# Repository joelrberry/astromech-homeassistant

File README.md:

# droidrefit — an offline-first astromech droid

Custom MicroPython firmware for a stationary R2-D2 display build. It runs
**standalone** — three front-panel buttons drive the dome servo, sound, and
dome lights (tap mode ▲ / ▼ to cycle reactions, hold to adjust volume, tap
sound for a clip), with a piezo buzzer for feedback. WiFi + **Home Assistant**
(pick a reaction from a dashboard) are an optional layer, off by default; hold
**Mode ▲ + Sound** ~5 s to set up WiFi. No RC transmitter.

> **Repo name is historical.** This started as a firmware swap on a *CyberBrick*
> ESP32-C3 core board. That board browned out under servo + NeoPixels + WiFi,
> so the project moved to a plain **ESP32** with an external 5 V supply and a
> from-scratch modular firmware. The reverse-engineering writeup from that first
> chapter is [docs/cyberbrick-origins.md](docs/cyberbrick-origins.md).

## What's here

| Path | What |
|---|---|
| [`droidrefit/`](droidrefit/) | the firmware — `app/` package, `lib/`, `boot.py`, `main.py`, `package.json` (OTA manifest) |
| [`tools/deploy.py`](tools/deploy.py) | one-command host→board sync (`mpremote`), also the initial-load tool |
| [`hardware/droidrefit-pcb/`](hardware/droidrefit-pcb/) | KiCad carrier board — sockets the ESP32 devkit + DFPlayer, one 5 V rail, USB-C in. [DESIGN.md](hardware/droidrefit-pcb/DESIGN.md) |
| [`docs/firmware.md`](docs/firmware.md) | **the firmware reference** — architecture, boot flow, control surfaces, OTA, recovery |
| [`docs/dfplayer.md`](docs/dfplayer.md) | DFPlayer Mini — SD-card layout, adding sound clips, the serial protocol |
| [`docs/cyberbrick-origins.md`](docs/cyberbrick-origins.md) | the original CyberBrick writeup (retired board, but the LED/MQTT approach carried forward) |
| [`docs/project-notes.md`](docs/project-notes.md) | running history — decisions, bugs found and fixed |

## Hardware (as-built)

Plain ESP32 devkit · one dome servo (GPIO18) · DFPlayer Mini + speaker
(GPIO16/17, BUSY GPIO4) · 4× WS2812 dome lights (GPIO5, via a `74AHCT1G125`
level shifter) · 3 buttons (GPIO32/33/25, pin↔GND) · piezo buzzer (GPIO27) ·
optional SSD1306 OLED (I2C, GPIO21/22) · a shared **5 V, 3 A+**
rail everything hangs off directly. The
[carrier PCB](hardware/droidrefit-pcb/DESIGN.md) (100×70 mm, USB-C in,
JLCPCB-assembled) makes that permanent; a breadboard works for bench work if
you power the ESP32 over its own USB.

## Quick start

```
pip install mpremote
python3 tools/deploy.py --wipe
```

`deploy.py` stages the copy in safe mode and SHA-verifies every file, retrying
over a flaky USB link; a failed run leaves the board at a safe REPL, and
re-running converges. `--stay` leaves it in safe mode; `--format` reformats
the flash (last resort).

> **After flashing, hard power-cycle the board** (pull power / press EN — not
> just a soft reset). `deploy.py` ends with a soft reset, but hardware timers,
> the UART, PWM, and singleton driver objects survive that; only a cold boot
> gives the clean state the firmware actually runs in.

It boots straight into the app, **offline**. Buttons: **tap** mode ▲ / ▼ to
cycle the 7 reactions, **hold** to raise / lower volume, tap Sound for a clip.
The buzzer beeps to confirm.

**To add Home Assistant:** hold **Mode ▲ + Sound** together ~5 s → the board
reboots into a WiFi AP **`R2-D2-XXXX`**. Join it from a phone, the setup page
opens, enter WiFi + a droid name (tick "Connect to Home Assistant" for the MQTT
broker fields), save. It reboots onto your network and HA auto-discovers it
over MQTT (Mode / Sound / Volume + diagnostic sensors). No always-on web panel;
the portal exits on its own after 5 min idle, or via its Cancel link.

**Updates go over USB** — after an edit, `python3 tools/deploy.py`. On-device
OTA exists but is opt-in, needs `network_enabled`, and — on a classic ESP32 —
a plain-HTTP LAN mirror (`ota_url`), because it can't TLS to GitHub while the
app runs. Detail in [docs/firmware.md](docs/firmware.md).

## Recovery

- `noboot.txt` at the flash root → boot straight to a clean REPL (`deploy.py` uses this)
- hold **Mode ▲ + Sound** ~5 s → reboot into the WiFi setup portal (auto-exits after 5 min idle)
- hold the ESP32 BOOT button ~10 s while running → factory reset (wipe config, reboot to portal)
- a crash-looping OTA build auto-rolls-back after 3 failed boots

## Credits

- **The droid** — [*Build-A-Droid: CyberBrick based robot kit*](https://makerworld.com/en/models/1549117-build-a-droid-cyberbrick-based-robot-kit)
  by **Neebick** on MakerWorld. That's the printed astromech this firmware
  drives; this repo is only the electronics + software, not the model.
  Licensed Creative Commons (see the model page for the exact variant and
  follow its attribution / non-commercial / share-alike terms).
- **`droidrefit/lib/umqtt/simple.py`** — vendored **unmodified** from
  [micropython-lib](https://github.com/micropython/micropython-lib/blob/master/micropython/umqtt.simple/umqtt/simple.py)
  (MIT). MicroPython ships no MQTT client.
- **`droidrefit/lib/dfplayer.py`** — a minimal DFPlayer Mini (YX5200) UART
  driver written for this project; the frame/checksum protocol is per the
  DFPlayer Mini datasheet and the widely-published community command tables,
  not copied from a specific library.
- **`droidrefit/lib/ssd1306.py`** — vendored from
  [micropython-lib](https://github.com/micropython/micropython-lib/blob/master/micropython/drivers/display/ssd1306/ssd1306.py)
  (MIT), SPI variant trimmed off.
- **[MicroPython](https://micropython.org/)** (MIT) — the runtime.
- The earlier CyberBrick chapter leaned on CyberBrick's own `/bbl` driver
  library — see [docs/cyberbrick-origins.md](docs/cyberbrick-origins.md#acknowledgments).

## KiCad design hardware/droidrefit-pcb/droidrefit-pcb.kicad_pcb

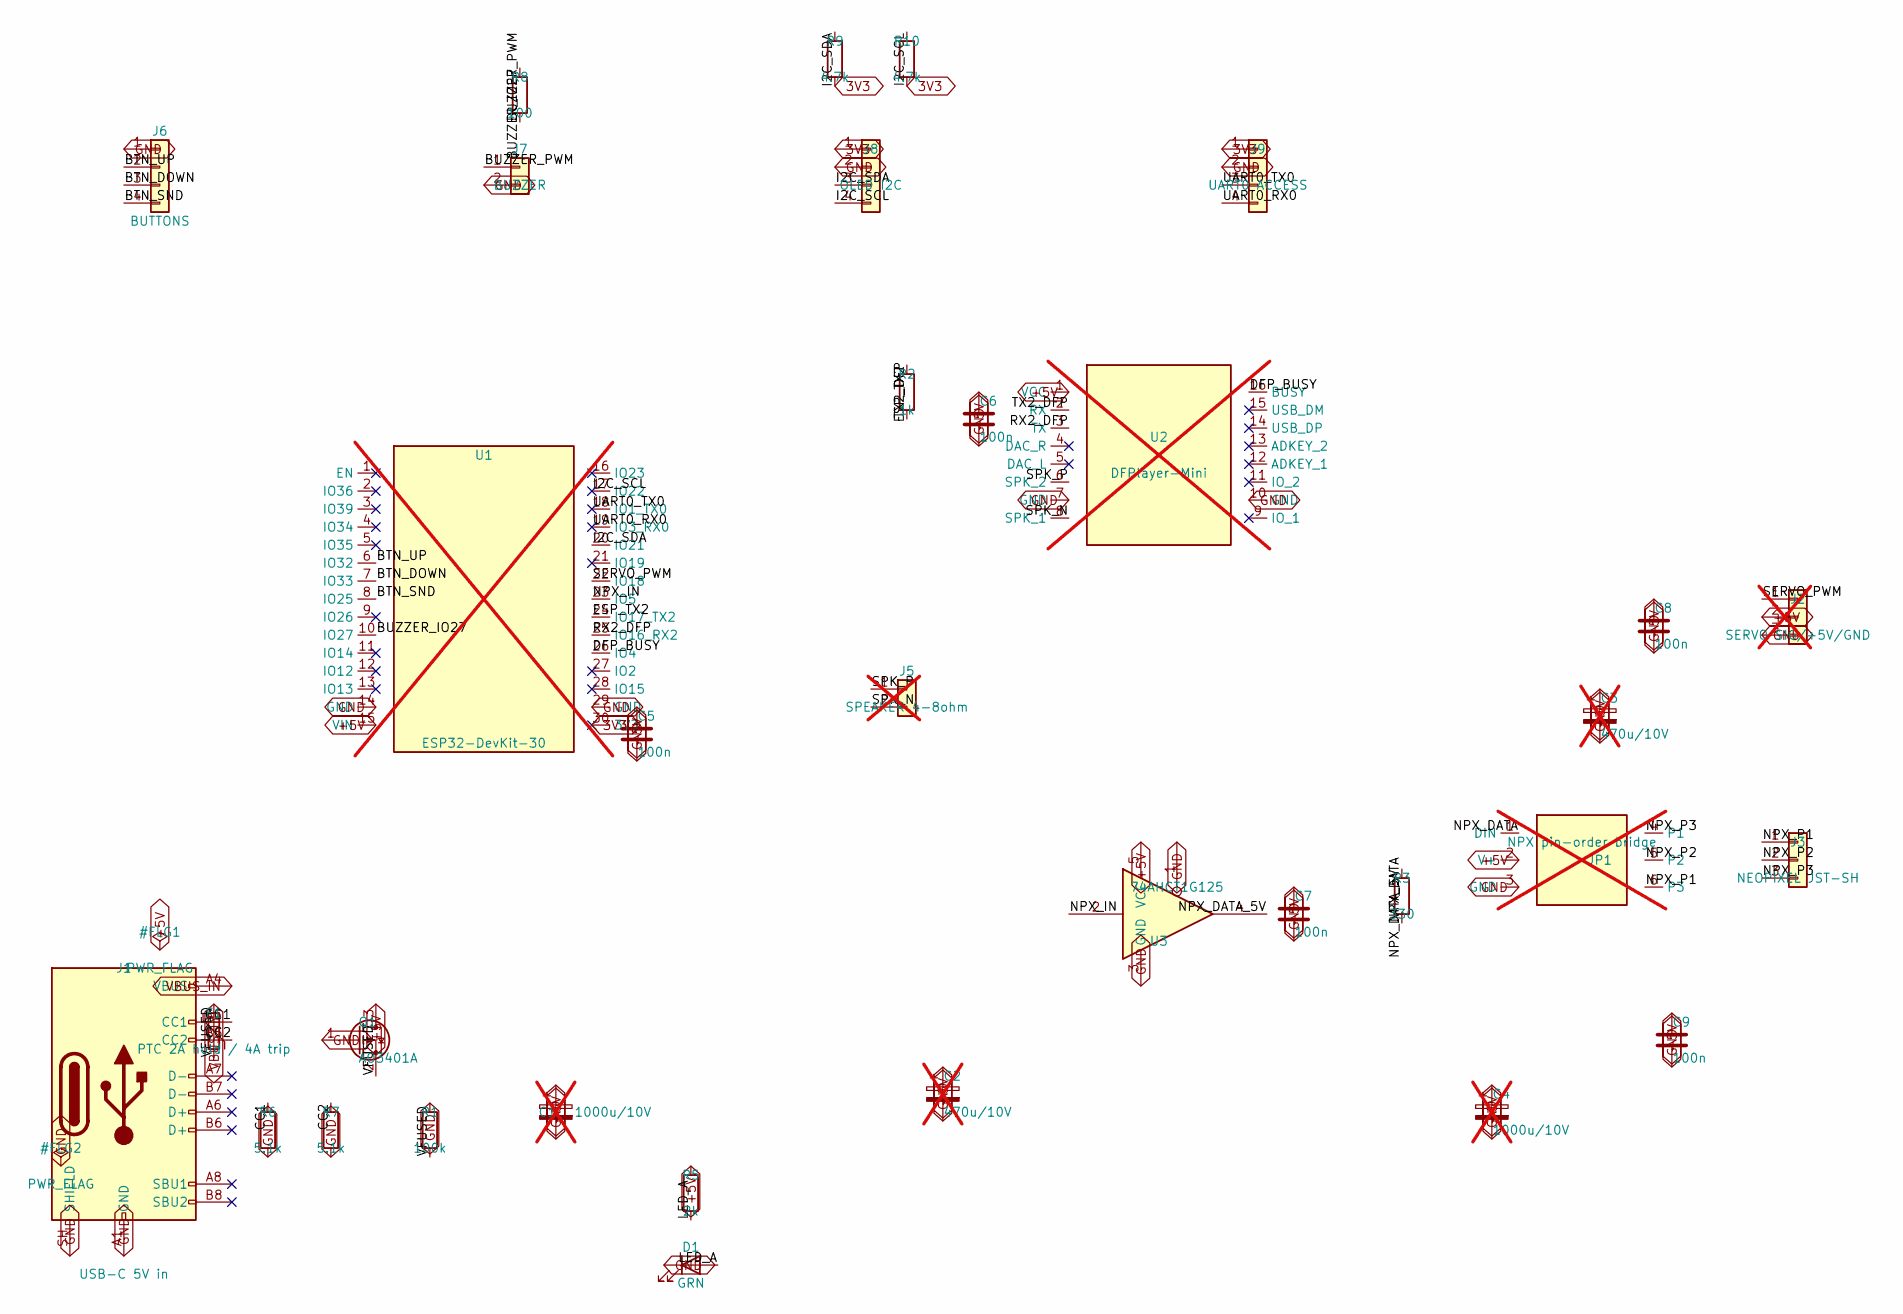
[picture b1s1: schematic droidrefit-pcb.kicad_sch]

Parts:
C1, C4: 1000u/10V; CP_Elec_8x10.5; MPN RVE1A102M0810; LCSC C310838; not fitted
C2, C3: 470u/10V; CP_Elec_6.3x7.7; MPN RVT1A471M0607; LCSC C335982; not fitted
C5, C6, C7, C8, C9: 100n; C_0603_1608Metric; MPN CC0603KRX7R9BB104; LCSC C14663
D1: GRN; LED_0603_1608Metric; MPN XL-1608UGC-04; LCSC C965804
F1: PTC 2A hold / 4A trip; Fuse_1812_4532Metric; MPN 1812L200/30GR; LCSC C18198342
J1: USB-C 5V in; USB_C_Receptacle_HCTL_HC-TYPE-C-16P-01A; MPN TYPE-C 16PIN 2MD; LCSC C2765186
J2: SERVO SIG/+5V/GND; PinHeader_1x03_P2.54mm_Vertical; MPN 1x3 2.54mm header; LCSC C49257; not fitted
J3: NEOPIXEL JST-SH; JST_SH_BM03B-SRSS-TB_1x03-1MP_P1.00mm_Vertical; MPN BM03B-SRSS-TB(LF)(SN); LCSC C160389
J5: SPEAKER 4-8ohm; JST_PH_B2B-PH-K_1x02_P2.00mm_Vertical; MPN B2B-PH-K-S; LCSC C131337; not fitted
J6: BUTTONS; PinHeader_1x04_P2.54mm_Vertical
J7: BUZZER; PinHeader_1x02_P2.54mm_Vertical
J8: OLED I2C; PinHeader_1x04_P2.54mm_Vertical
J9: UART0 ACCESS; PinHeader_1x04_P2.54mm_Vertical
JP1: NPX pin-order bridge; NeoPixel_Cfg_BridgeField_6; not fitted
Q1: AO3401A; SOT-23; MPN AO3401A; LCSC C15127
R1: 100k; R_0603_1608Metric; MPN 0603WAF1003T5E; LCSC C25803
R2: 1k; R_0603_1608Metric; MPN 0603WAF1001T5E; LCSC C21190
R3: 330; R_0603_1608Metric; MPN 0603WAF3300T5E; LCSC C23138
R5: 2k; R_0603_1608Metric; MPN 0603WAF2001T5E; LCSC C22975
R6, R7: 5.1k; R_0603_1608Metric; MPN 0603WAF5101T5E; LCSC C23186
R8: 100; R_0603_1608Metric
R9, R10: 4.7k; R_0603_1608Metric
U1: ESP32-DevKit-30; ESP32_DevKit_30pin_Socket_24p5mm; not fitted
U2: DFPlayer-Mini; DFPlayer_Mini_Socket; not fitted
U3: 74AHCT1G125; SOT-23-5; MPN SN74AHCT1G125DBVR; LCSC C7484

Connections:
3V3: J8.1, J9.1, R9.2, R10.2, U1.30 (3V3)
+5V: C1.1, C2.1, C3.1, C4.1, C5.1, C6.1, C7.1, C8.1, C9.1, J2.2, JP1.2 (V+), Q1.3 (D), R5.1, U1.15 (VIN), U2.1 (VCC), U3.5 (VCC)
BTN_DOWN: J6.3, U1.7 (IO33)
BTN_SND: J6.4, U1.8 (IO25)
BTN_UP: J6.2, U1.6 (IO32)
BUZZER_IO27: R8.1, U1.10 (IO27)
BUZZER_PWM: J7.1, R8.2
CC1: J1.A5 (CC1), R6.1
CC2: J1.B5 (CC2), R7.1
DFP_BUSY: U1.26 (IO4), U2.16 (BUSY)
ESP_TX2: R2.1, U1.24 (IO17_TX2)
GND: C1.2, C2.2, C3.2, C4.2, C5.2, C6.2, C7.2, C8.2, C9.2, D1.1 (K), J1.A1 (GND), J1.A12 (GND), J1.B1 (GND), J1.B12 (GND), J1.SH (SHIELD), J2.3, J6.1, J7.2, J8.2, J9.2, JP1.3 (GND), Q1.1 (G), R1.1, R6.2, R7.2, U1.14 (GND), U1.29 (GND), U2.7 (GND), U2.10 (GND), U3.1, U3.3 (GND)
I2C_SCL: J8.4, R10.1, U1.17 (IO22)
I2C_SDA: J8.3, R9.1, U1.20 (IO21)
LED_A: D1.2 (A), R5.2
NPX_DATA: JP1.1 (DIN), R3.2
NPX_DATA_5V: R3.1, U3.4
NPX_IN: U1.23 (IO5), U3.2
NPX_P1: J3.1, JP1.6 (P3)
NPX_P2: J3.2, JP1.5 (P2)
NPX_P3: J3.3, JP1.4 (P1)
RX2_DFP: U1.25 (IO16_RX2), U2.3 (TX)
SERVO_PWM: J2.1, U1.22 (IO18)
SPK_N: J5.2, U2.8 (SPK_1)
SPK_P: J5.1, U2.6 (SPK_2)
TX2_DFP: R2.2, U2.2 (RX)
UART0_RX0: J9.4, U1.19 (IO3_RX0)
UART0_TX0: J9.3, U1.18 (IO1_TX0)
VBUS_IN: F1.1, J1.A4 (VBUS), J1.A9 (VBUS), J1.B4 (VBUS), J1.B9 (VBUS)
VFUSED: F1.2, Q1.2 (S), R1.2

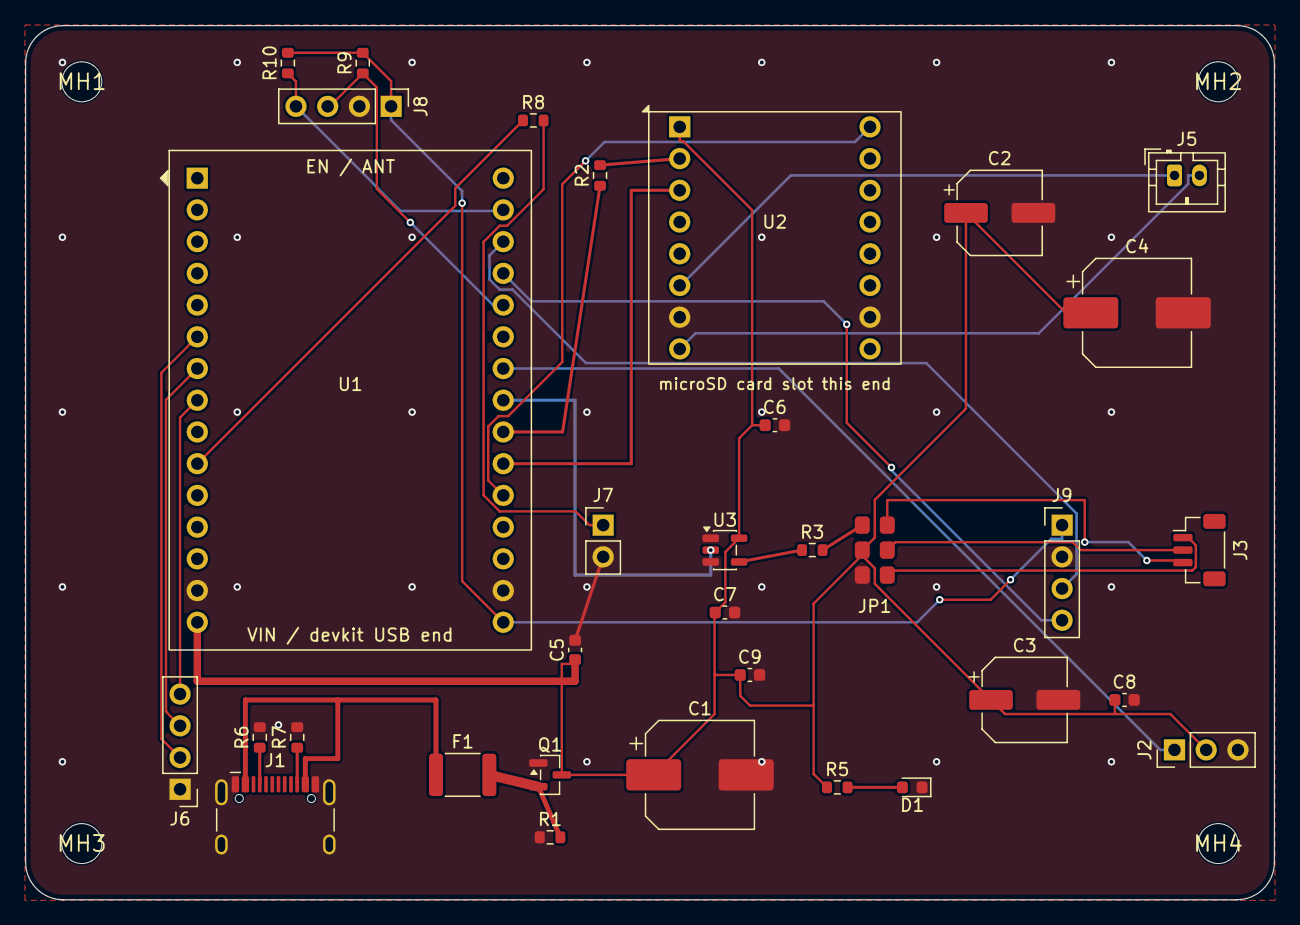
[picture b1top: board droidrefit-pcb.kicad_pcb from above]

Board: 2 copper layers, 100.0 x 70.0 mm, 37 parts (0 on the bottom side), 30 nets.

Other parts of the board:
MH1, MH2, MH3, MH4: MountingHole_3.2mm

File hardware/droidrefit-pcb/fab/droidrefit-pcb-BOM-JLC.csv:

Comment,Designator,Footprint,LCSC
1000u/10V,"C1,C4",CP_Elec_8x10.5,
470u/10V,"C2,C3",CP_Elec_6.3x7.7,
100n,"C5,C6,C7,C8,C9",C_0603_1608Metric,
GRN,D1,LED_0603_1608Metric,
PTC 2A hold / 4A trip,F1,Fuse_1812_4532Metric,
USB-C 5V in,J1,USB_C_Receptacle_HCTL_HC-TYPE-C-16P-01A,
NEOPIXEL JST-SH,J3,JST_SH_BM03B-SRSS-TB_1x03-1MP_P1.00mm_Vertical,
P-MOSFET revpol,Q1,SOT-23,
100k,R1,R_0603_1608Metric,
1k,R2,R_0603_1608Metric,
330,R3,R_0603_1608Metric,
2k,R5,R_0603_1608Metric,
5.1k,"R6,R7",R_0603_1608Metric,
100,R8,R_0603_1608Metric,
4.7k,"R9,R10",R_0603_1608Metric,
74AHCT1G125,U3,SOT-23-5,
